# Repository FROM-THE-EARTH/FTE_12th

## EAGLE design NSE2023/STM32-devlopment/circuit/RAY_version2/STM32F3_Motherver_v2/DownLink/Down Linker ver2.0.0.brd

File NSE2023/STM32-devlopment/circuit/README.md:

# circuit

## 開発の流れ
RAY電装の開発は以下のような流れで行いました。
1. ブレッドボード上でのSTM32F303K8の動作試験
2. PCB基板上での書き込み試験(LED点灯プログラム)
3. PCB基板上でのprintfデバッグ
4. PCB基板上でのサーボモーターの動作試験
5. PCB基板上でのI2Cデバイスの動作試験(BNO055,BMP180)
6. PCB基板上でのSDカードの動作試験
7. PCB基板上でのUARTデバイスの動作試験(GPS,RM92A)  

各項目について、詳細な手順を以下に記載します。
### ブレッドボード上でのSTM32F303K8の動作試験
電装製作において最も重要なことは手を動かすことです。未知な要素が多いマイコンを扱う際は、早めに部品を発注して動作試験をしましょう。
筆者はまず[このサイト](https://yoshikiyo.com/2021/01/04/20210104/)を参考にSTM32の動作試験を行いました。実際に使用した部品を以下に記載します。
* [STM32F303K8](https://akizukidenshi.com/catalog/g/gI-10790/)
* [32ピンQFR変換基板](https://akizukidenshi.com/catalog/g/gP-09581/)
* [STLink](https://www.amazon.co.jp/QuiExact-%E3%83%97%E3%83%AD%E3%82%B0%E3%83%A9%E3%83%9F%E3%83%B3%E3%82%B0%E3%82%AD%E3%83%83%E3%83%88-%E3%82%A8%E3%83%9F%E3%83%A5%E3%83%AC%E3%83%BC%E3%82%BF%E3%83%87%E3%83%90%E3%83%83%E3%82%AC-%E3%82%B7%E3%83%9F%E3%83%A5%E3%83%AC%E3%83%BC%E3%82%B7%E3%83%A7%E3%83%B3-%E3%83%87%E3%83%90%E3%83%83%E3%82%AC%E3%82%A8%E3%83%9F%E3%83%A5%E3%83%AC%E3%83%BC%E3%82%BF/dp/B0B5KLKDY2/ref=sr_1_1_sspa?keywords=st-link%2Fv2&qid=1698780781&sr=8-1-spons&sp_csd=d2lkZ2V0TmFtZT1zcF9hdGY&psc=1)

接続するピンさえ間違えなければ、サイトの手順に従うことでLEDの点灯プログラムの動作試験を完了させることができると思います。
マイコンボードと違いUSBインターフェースがないため、書き込みにはSTLinkと呼ばれる専用の書き込み装置を用いる必要があります。中華性の格安STLinkではなく、純正品を使用することをおすすめします。

### PCB基板上での書き込み試験(LED点灯プログラム)
上記のサイトをもとに、以下のような回路を設計しました。

電源系はサイトに準拠し、I2Cデバイス(BNO055, BMP180)及びmicroSDのインターフェースを設けました。この基板を用いてLED点灯プログラム及びprintfデバッグ、I2Cデバイスの動作試験を正常に行うことができました。この基板でのSDカードの書き込みには成功していないため、SDカードの動作試験には別基板を用いる必要があります。(後述)

### PCB基板上でのprintfデバッグ
マイコンからPCへのデータの送信を確立することは組み込み開発における必須事項です。マイコンボードを使用する場合はUSBインターフェースがあるため別途容易する必要はありませんが、マイコン単体から開発する場合は自分で回路上にPC用のインターフェースを用意する必要があります。  

STM32マイコンにはSWOと呼ばれるピンが用意されており、手元にあるSTLinkのSWOピンと接続することで、SWO通信を利用することができます。SWOはUARTのTXピンと同等の役割を果たし、マイコンからPCにprintfを介してデータを送信することができます。  

筆者は[このサイト](https://yukblog.net/stm32cubeide-printf-swo/)をもとにSWOによるprintfの動作試験を行いました。基本的にはサイトに従う形でかまいませんが、1.12以降のCubeIDEを用いる場合は追加で以下の設定が必要です。
project内のiocファイルを開き、System Core > SYSを加え、写真の通りに設定を行ってください。

これにより、printfツールを正常に使用することができるはずです。また、printfツールでfloat型の変数を表示したい場合は[追加設定](https://yukblog.net/stm32cubeide-printf-float/)が必要です。　　

陥りやすいミスと対策法を以下に示します。
* STLinkとの接続ミス(ピンの名前が書いてないため間違えやすい)
* 過剰に高い周波数で動作させている。外部発振器を用いない場合STM32F303K8で利用可能な最大周波数は64MHzですが、32MHz程度で動作させることを推奨します。ロケット電装でそこまで高周波で動作することは求められることはありませんし、高周波になるほどノイズがのりやすくなります。
* プログラムに問題があるか、表示のさせ方に問題があるかを明らかにするために、オシロスコープを用いることを推奨します。オシロスコープのプローブをGNDとSWOピンに接続し、そもそも信号が走っているかを確認しましょう。

### PCB基板上でのサーボモーターの動作試験
サーボモーターの駆動にはPWM信号を出力する必要があり、PWM信号の出力にはタイマーの利用が必須です。  
STM32F303K8ではTIM1,2,3,6,7,15,16,17の合計8つのタイマーを利用することができます。SWOやUARTもタイマーを使用するため、空き状況をみて適切なタイマーを選択してください。筆者はTIM2のchannel1を使用しています。

```cpp
/* USER CODE BEGIN 2 */
	HAL_TIM_PWM_Start(&htim2, TIM_CHANNEL_1); //initialize PWM
/* USER CODE END 2 */
```

サーボモーターの動作試験に関して最も参考になるのは[このサイト](https://qiita.com/usashirou/items/2d0fedf59a3cef083b87)だと思います。  
参考までに筆者の動作試験時の設定を共有します。
* APB1 Timer clocks (MHz) : 44MHz
* Prescaler(PSC - 16 bits value) : 840
* Counter Period : 1048

sg90を使用する場合は以下の関数をそのまま流用することができます。
```cpp
/* USER CODE BEGIN 4 */
void servoWrite(int angle) {
	// Calculate pulse value based on the angle
	int pulseValue = 25 + angle * (120 - 25) / 180;

	// Ensure pulseValue is within valid range
	if (pulseValue > 120) {
		pulseValue = 120;
	}

	// Set the pulse width using TIM2 and specified channel
	__HAL_TIM_SET_COMPARE(&htim2, TIM_CHANNEL_1, pulseValue);
}
/* USER CODE END 4 */
```

### PCB基板上でのI2Cデバイスの動作試験
特別な設定はいりません。詳細は /software に記載します。

### PCB基板上でのSDカードの動作試験
おそらく最も苦戦するのがSDカードの書き込みです。ここでは回路上の注意事項を述べたいと思います。

SDカードの書き込みにはSPI通信を用いています。SPI通信は大容量のデータ転送を可能にする高速な通信ですが、高周波であるためにノイズに弱いという特性を持っています。配線時にノイズを軽減する配慮をしなければ、書き込みに失敗してしまうでしょう。以下にノイズを軽減する有効な手段を示します。
* MISO, MOSI, CLKラインのプルアップ。1k~10kの抵抗でプルアップしてください。筆者は1kΩの抵抗を使用していました。
* ダンピング抵抗の設置。CLK出力ピンの直後に100Ω程度の抵抗を配置することで、ノイズを減衰させることができます。[(参考サイト)](https://ally-japan.jimdo.com/2015/11/23/%E3%82%AF%E3%83%AD%E3%83%83%E3%82%AF%E3%81%AB%E3%81%A4%E3%81%84%E3%81%A6-part2/)
* 配線の最短化。基本的に、配線は長いほど、細いほどノイズがのりやすくなります。SDカードへの配線は可能な限り短く、太くすべきです。

完全ではありませんが、上記の3点に留意した以下の基板では、SDカードの書き込みに成功しています。  

### PCB基板上でのUARTデバイスの動作試験
GPS、RM92Aともに特別な設定はいりませんが、RM92Aは13期代にとって初めて使用する無線モジュールになるので、簡単な使用法をここで紹介します。  
回路の情報は[データシート](http://www.cec-chiyoda.co.jp/document/rflink_RM-92A_RM-92C.pdf)を参考にしてください。一般的な無線モジュールと同様にRX,TXのピンをマイコンに接続すれば問題なく使用することができます。  
データシートに従えば回路構成は以下のようになります。 
  
PIN13は無線のパラメータ設定時にHIGHとLOWを切り替える必要があるため、図のようにスライドスイッチを介してGNDに接続しています。  
RM92Aを導入した背景は、IM920では海打ち機体において十分な通信距離を確保できないため、より長い距離通信できる無線モジュールが必要だったからです。RM92Aは見通し最大100kmの通信が可能であり、一般的な条件下でも10km以上の通信が可能であると言われています。特別な理由がなければ海打ち機体にはIM920ではなくRM92Aを搭載することを推奨します。

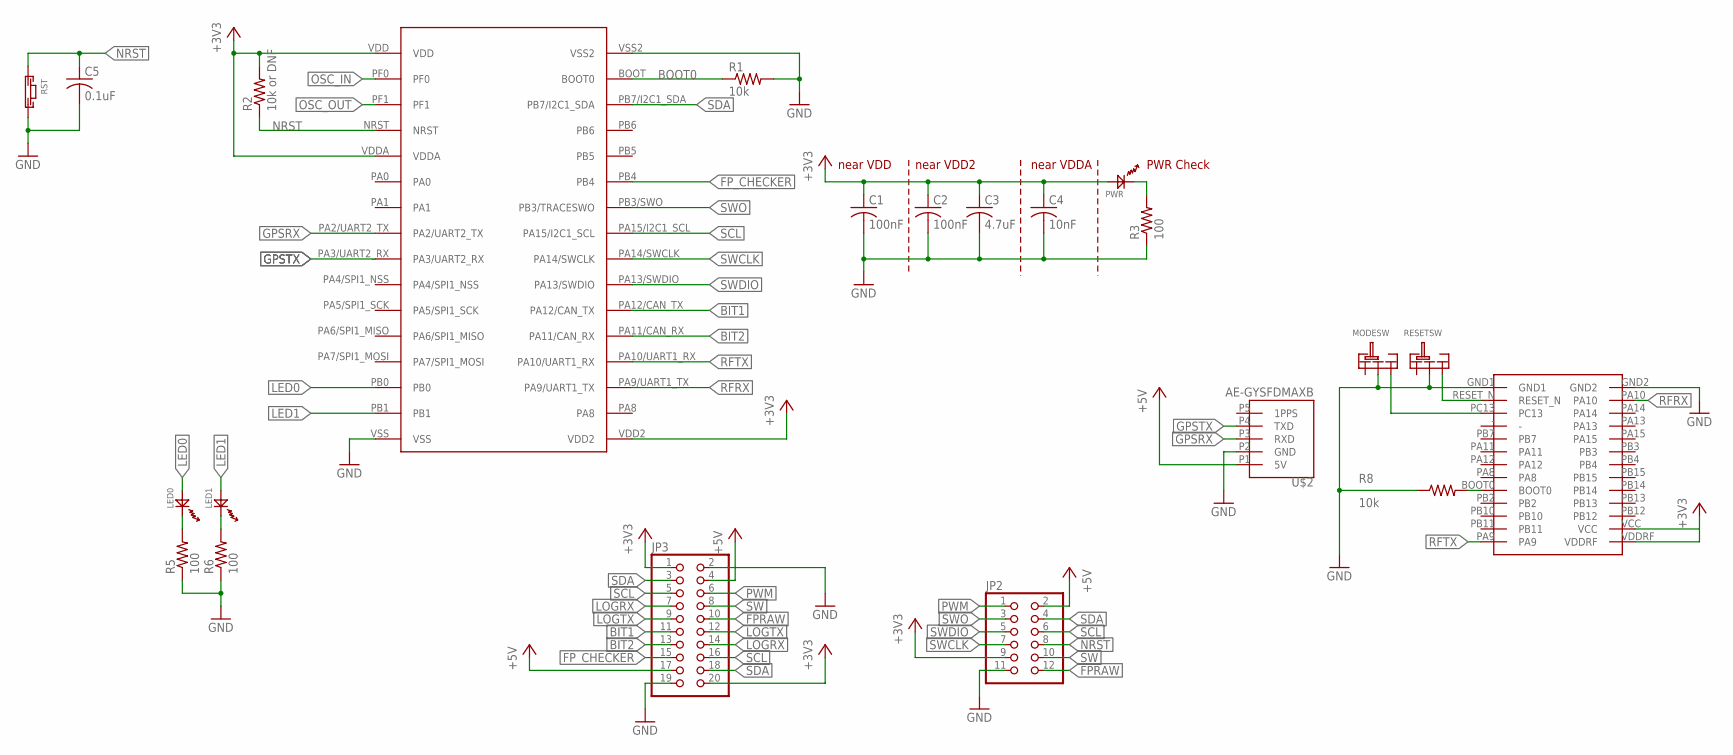
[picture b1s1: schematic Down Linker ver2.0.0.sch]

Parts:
C1, C2: 100nF; C1608
C3: 4.7uF; C1608
C4: 10nF; C1608
C5: 0.1uF; C1608
JP2: PINHD-2X6/90; 2X06/90
JP3: PINHD-2X10/90; 2X10/90
LED0, LED1: OSXX1608C1A
MODESW: SRIDE_SWITCH
PWR: OSXX1608C1A
R1, R8: 10k; R0603
R2: 10k or DNF; R0603
R3, R5, R6: 100; R0603
RESETSW: SRIDE_SWITCH
RST: TVAF06-A020B-R
U$1: STM32F303K8
U$2: AE-GYSFDMAXB
U$3: RM-92A

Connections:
+3V3: C1.1, C2.1, C3.1, C4.1, JP2.9, JP3.1, JP3.20, PWR.AN, R2.2, U$1.VDD, U$1.VDD2, U$1.VDDA, U$3.VCC, U$3.VDDRF
+5V: JP2.2, JP3.4, JP3.17, U$2.P1 (5V)
BIT1: JP3.11, U$1.PA12/CAN_TX
BIT2: JP3.13, U$1.PA11/CAN_RX
BOOT0: R1.1, U$1.BOOT (BOOT0)
FPRAW: JP2.12, JP3.10
FP_CHECKER: JP3.15, U$1.PB4
GND: C1.2, C2.2, C3.2, C4.2, C5.2, JP2.11, JP3.2, JP3.19, MODESW.LR, R1.2, R3.1, R5.1, R6.1, R8.1, RESETSW.LR, RST.P$2, U$1.VSS, U$1.VSS2, U$2.P2 (GND), U$3.GND1, U$3.GND2
GPSRX: U$1.PA2/UART2_TX, U$2.P3 (RXD)
GPSTX: U$1.PA3/UART2_RX, U$2.P4 (TXD)
LED0: LED0.AN, U$1.PB0
LED1: LED1.AN, U$1.PB1
LOGRX: JP3.7, JP3.14
LOGTX: JP3.9, JP3.12
unnamed: PWR.CT, R3.2
unnamed: LED0.CT, R5.2
unnamed: LED1.CT, R6.2
unnamed: MODESW.R, U$3.PC13
unnamed: RESETSW.R, U$3.RESET_N
unnamed: R8.2, U$3.BOOT0
NRST: C5.1, JP2.8, R2.1, RST.P$1, U$1.NRST
OSC_IN: U$1.PF0
OSC_OUT: U$1.PF1
PWM: JP2.1, JP3.6
RFRX: U$1.PA9/UART1_TX, U$3.PA10
RFTX: U$1.PA10/UART1_RX, U$3.PA9
SCL: JP2.6, JP3.5, JP3.16, U$1.PA15/I2C1_SCL
SDA: JP2.4, JP3.3, JP3.18, U$1.PB7/I2C1_SDA
SW: JP2.10, JP3.8
SWCLK: JP2.7, U$1.PA14/SWCLK
SWDIO: JP2.5, U$1.PA13/SWDIO
SWO: JP2.3, U$1.PB3/SWO (PB3/TRACESWO)

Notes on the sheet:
near VDD
near VDD2
near VDDA
PWR Check

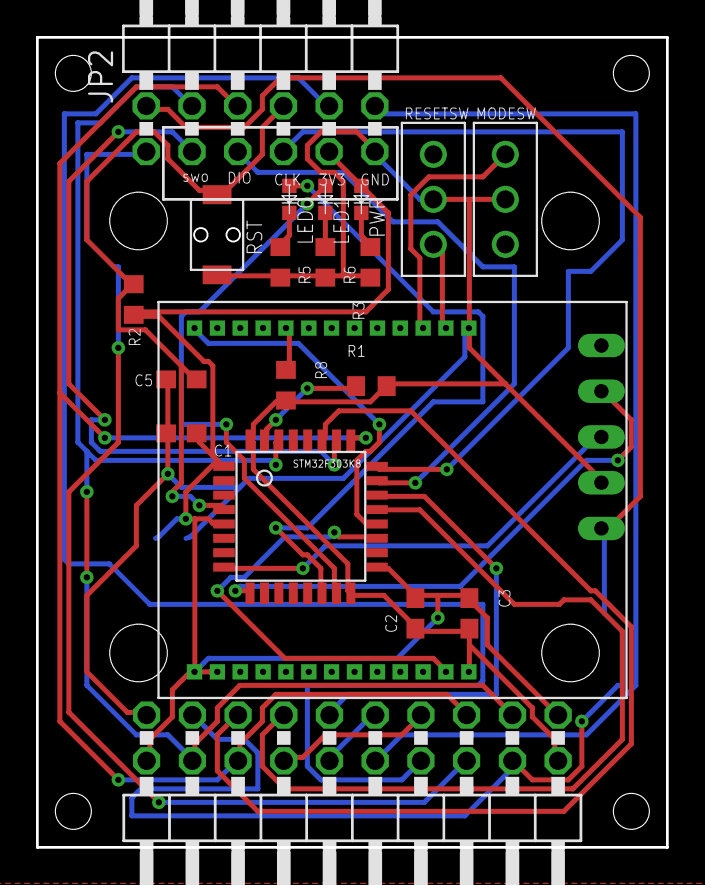
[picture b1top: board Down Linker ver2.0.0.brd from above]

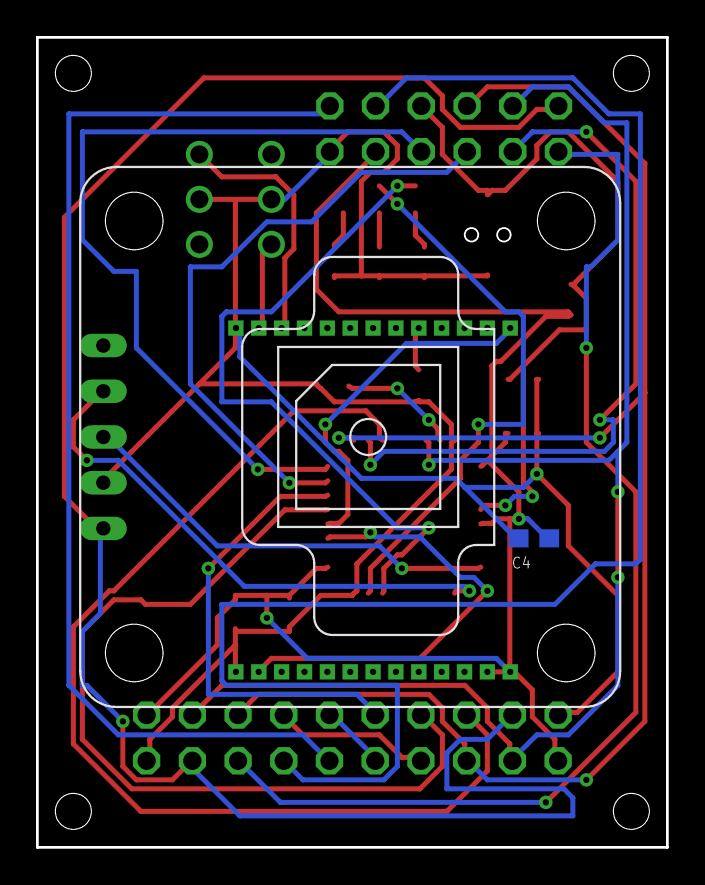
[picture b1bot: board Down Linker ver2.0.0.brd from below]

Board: 2 copper layers, 35.0 x 45.0 mm, 22 parts (2 on the bottom side), 30 nets.

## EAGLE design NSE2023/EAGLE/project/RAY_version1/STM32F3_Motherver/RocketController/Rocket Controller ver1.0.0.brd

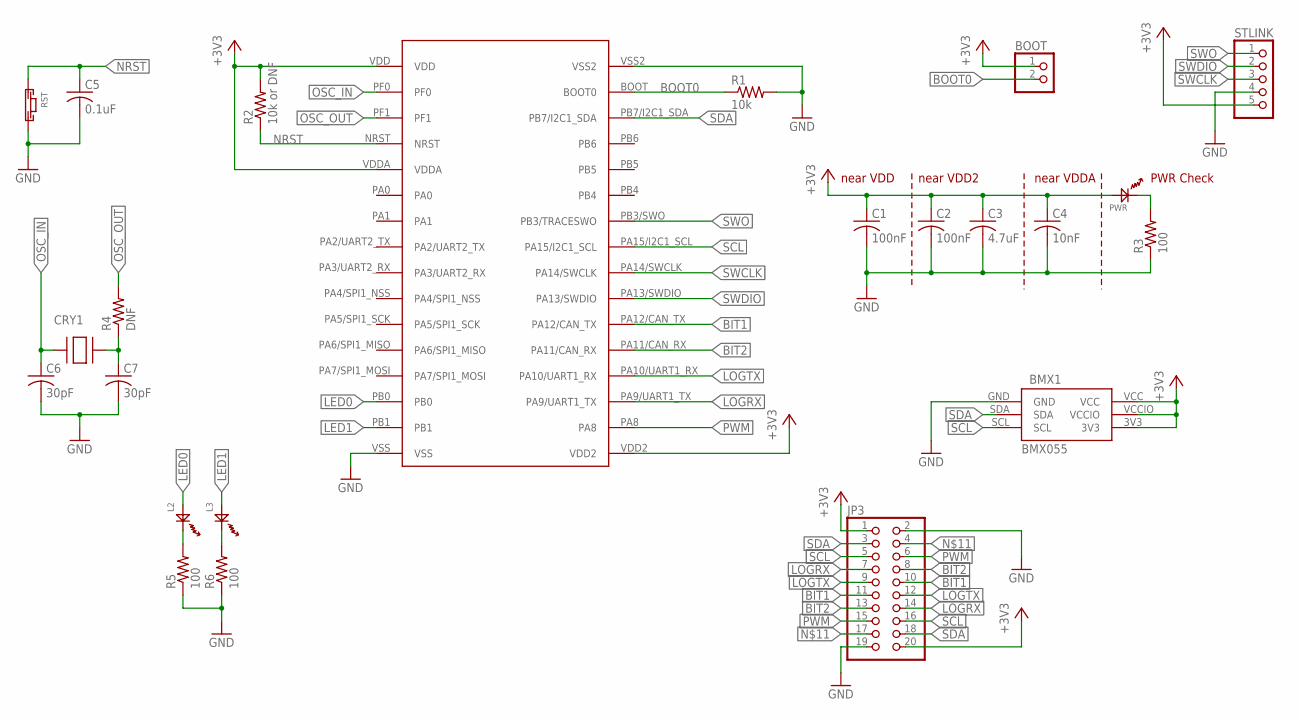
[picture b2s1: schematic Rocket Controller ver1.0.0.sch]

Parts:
BMX1: BMX055
BOOT: PINHD-1X2; 1X02
C1, C2: 100nF; C1608
C3: 4.7uF; C1608
C4: 10nF; C1608
C5: 0.1uF; C1608
C6, C7: 30pF; C1608
CRY1: 8MHZ; CRYSTAL
JP3: PINHD-2X10/90; 2X10/90
L2, L3: OSXX1608C1A
PWR: OSXX1608C1A
R1: 10k; R0603
R2: 10k or DNF; R0603
R3, R5, R6: 100; R0603
R4: DNF; R0603
RST: TVAF06-A020B-R
STLINK: PINHD-1X5; 1X05
U$1: STM32F303K8

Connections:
+3V3: BMX1.3V3, BMX1.VCC, BMX1.VCCIO, BOOT.1, C1.1, C2.1, C3.1, C4.1, JP3.1, JP3.20, PWR.AN, R2.2, STLINK.5, U$1.VDD, U$1.VDD2, U$1.VDDA
BIT1: JP3.10, JP3.11, U$1.PA12/CAN_TX
BIT2: JP3.8, JP3.13, U$1.PA11/CAN_RX
BOOT0: BOOT.2, R1.1, U$1.BOOT (BOOT0)
GND: BMX1.GND, C1.2, C2.2, C3.2, C4.2, C5.2, C6.2, C7.2, JP3.2, JP3.19, R1.2, R3.1, R5.1, R6.1, RST.P$2, STLINK.4, U$1.VSS, U$1.VSS2
LED0: L2.AN, U$1.PB0
LED1: L3.AN, U$1.PB1
LOGRX: JP3.7, JP3.14, U$1.PA9/UART1_TX
LOGTX: JP3.9, JP3.12, U$1.PA10/UART1_RX
unnamed: PWR.CT, R3.2
unnamed: L2.CT, R5.2
unnamed: C7.1, CRY1.P$2, R4.1
unnamed: L3.CT, R6.2
unnamed: JP3.4, JP3.17
NRST: C5.1, R2.1, RST.P$1, U$1.NRST
OSC_IN: C6.1, CRY1.P$1, U$1.PF0
OSC_OUT: R4.2, U$1.PF1
PWM: JP3.6, JP3.15, U$1.PA8
SCL: BMX1.SCL, JP3.5, JP3.16, U$1.PA15/I2C1_SCL
SDA: BMX1.SDA, JP3.3, JP3.18, U$1.PB7/I2C1_SDA
SWCLK: STLINK.3, U$1.PA14/SWCLK
SWDIO: STLINK.2, U$1.PA13/SWDIO
SWO: STLINK.1, U$1.PB3/SWO (PB3/TRACESWO)

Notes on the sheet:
near VDD
near VDD2
near VDDA
PWR Check

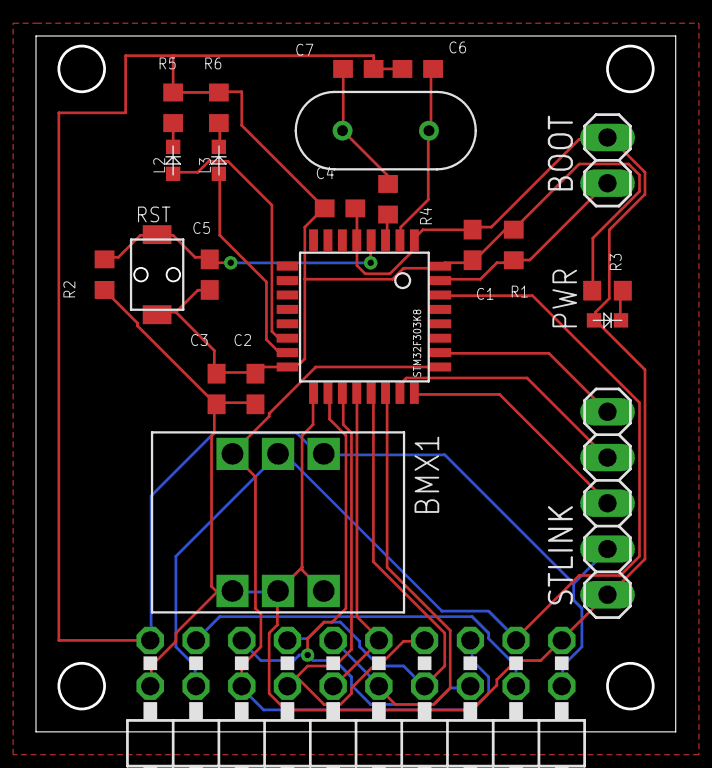
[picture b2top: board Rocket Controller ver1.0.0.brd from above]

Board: 2 copper layers, 35.4 x 38.5 mm, 23 parts (0 on the bottom side), 23 nets.

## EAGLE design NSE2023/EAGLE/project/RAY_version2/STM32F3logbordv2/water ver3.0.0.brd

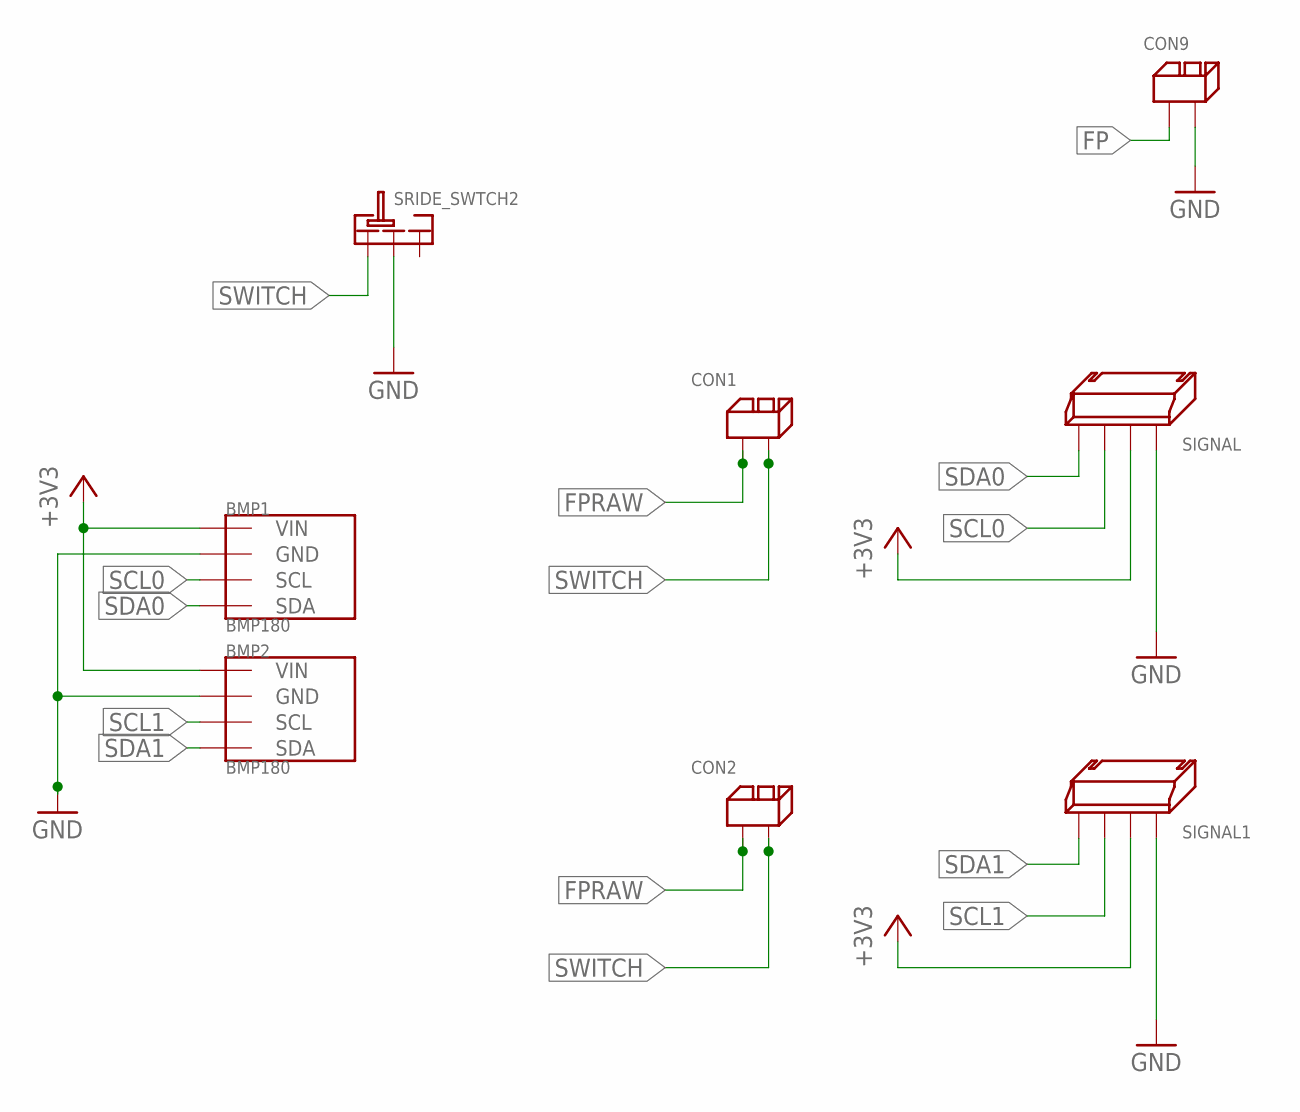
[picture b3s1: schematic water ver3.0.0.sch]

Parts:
BMP1, BMP2: BMP180; GY-68
CON1, CON2, CON9: 2PIN
SIGNAL, SIGNAL1: 4PIN_SIDE
SRIDE_SWTCH2: SRIDE_SWITCH

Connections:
+3V3: BMP1.P1 (VIN), BMP2.P1 (VIN), SIGNAL.P$3, SIGNAL1.P$3
FP: CON9.P$1
FPRAW: CON1.P$1, CON2.P$1
GND: BMP1.P2 (GND), BMP2.P2 (GND), CON9.P$2, SIGNAL.P$4, SIGNAL1.P$4, SRIDE_SWTCH2.LR
SCL0: BMP1.P3 (SCL), SIGNAL.P$1
SCL1: BMP2.P3 (SCL), SIGNAL1.P$1
SDA0: BMP1.P4 (SDA), SIGNAL.P$2
SDA1: BMP2.P4 (SDA), SIGNAL1.P$2
SWITCH: CON1.P$2, CON2.P$2, SRIDE_SWTCH2.L

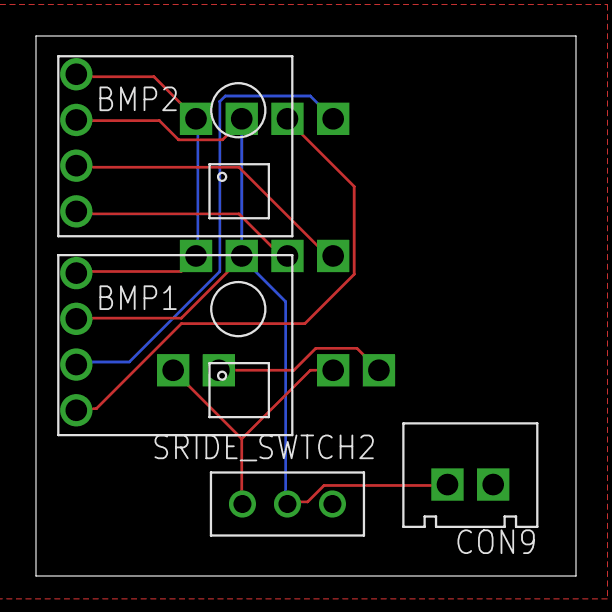
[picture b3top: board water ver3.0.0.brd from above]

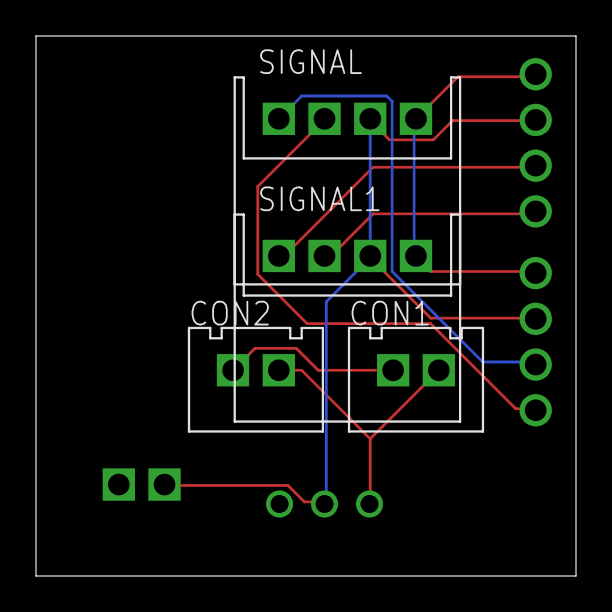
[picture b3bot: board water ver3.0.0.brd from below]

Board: 2 copper layers, 30.0 x 30.0 mm, 8 parts (4 on the bottom side), 8 nets.

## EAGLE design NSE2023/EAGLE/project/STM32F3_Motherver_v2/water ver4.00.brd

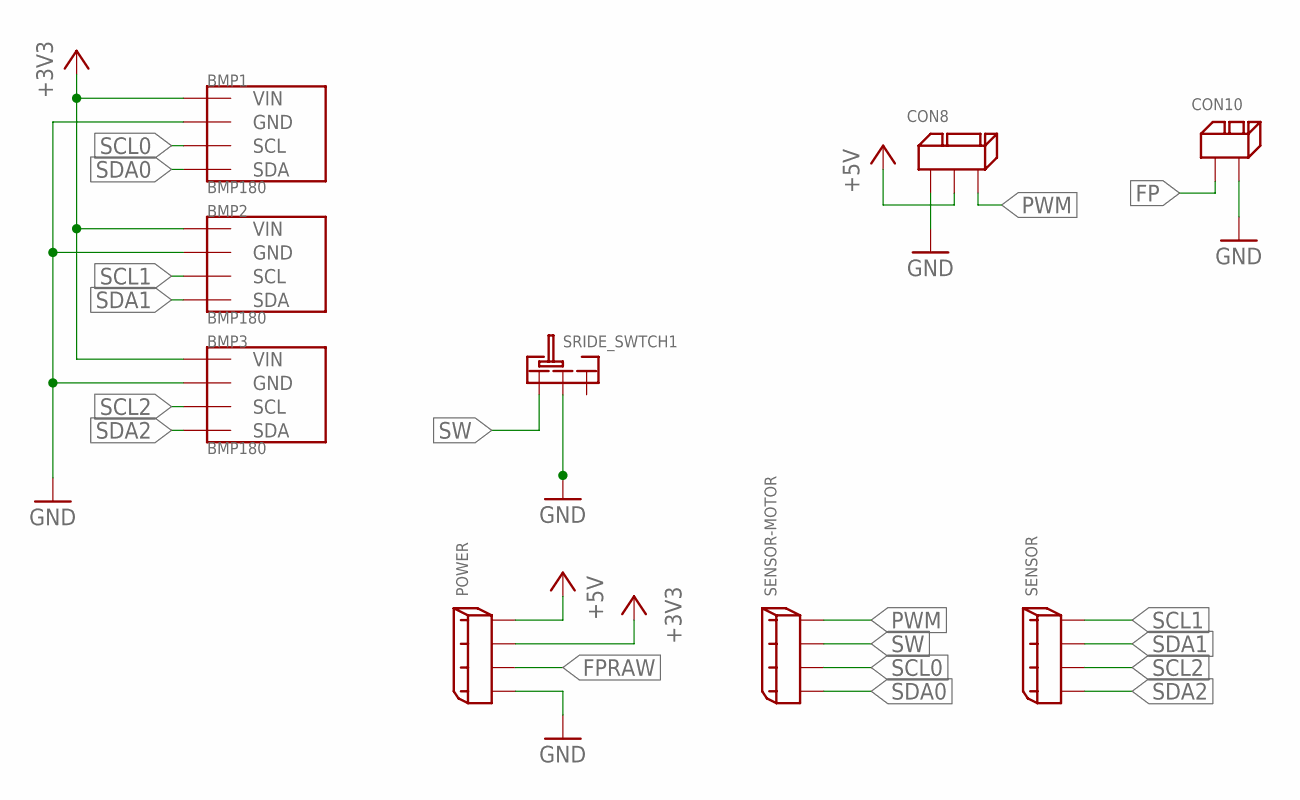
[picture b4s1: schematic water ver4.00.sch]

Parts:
BMP1, BMP2, BMP3: BMP180; GY-68
CON8: 3PIN
CON10: 2PIN
POWER: 2.5_MINI-SPOX_4PIN
SENSOR: 2.5_MINI-SPOX_4PIN
SENSOR-MOTOR: 2.5_MINI-SPOX_4PIN
SRIDE_SWTCH1: SRIDE_SWITCH

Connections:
+3V3: BMP1.P1 (VIN), BMP2.P1 (VIN), BMP3.P1 (VIN), POWER.P$3 (3)
+5V: CON8.P$2, POWER.P$4 (4)
FP: CON10.P$1
FPRAW: POWER.P$2 (2)
GND: BMP1.P2 (GND), BMP2.P2 (GND), BMP3.P2 (GND), CON8.P$1, CON10.P$2, POWER.P$1 (1), SRIDE_SWTCH1.LR
PWM: CON8.P$3, SENSOR-MOTOR.P$4 (4)
SCL0: BMP1.P3 (SCL), SENSOR-MOTOR.P$2 (2)
SCL1: BMP2.P3 (SCL), SENSOR.P$4 (4)
SCL2: BMP3.P3 (SCL), SENSOR.P$2 (2)
SDA0: BMP1.P4 (SDA), SENSOR-MOTOR.P$1 (1)
SDA1: BMP2.P4 (SDA), SENSOR.P$3 (3)
SDA2: BMP3.P4 (SDA), SENSOR.P$1 (1)
SW: SENSOR-MOTOR.P$3 (3), SRIDE_SWTCH1.L

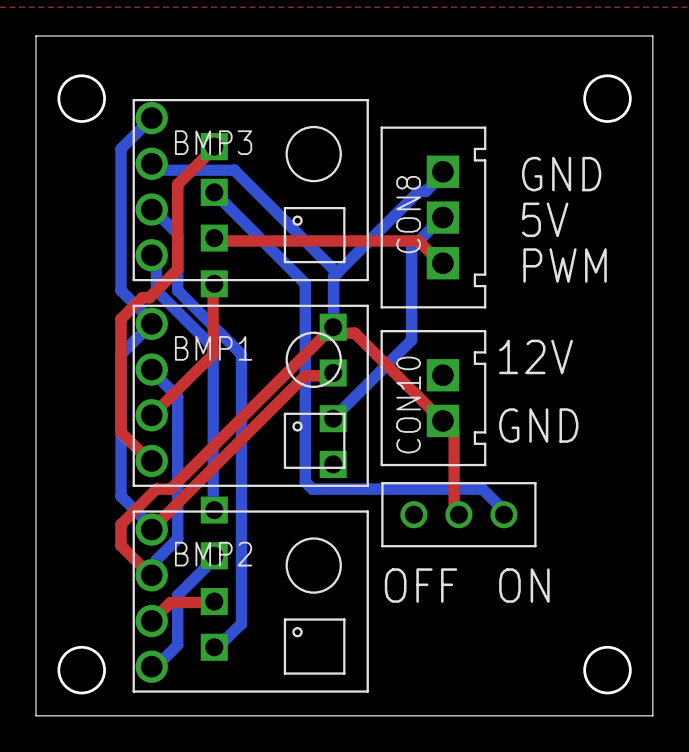
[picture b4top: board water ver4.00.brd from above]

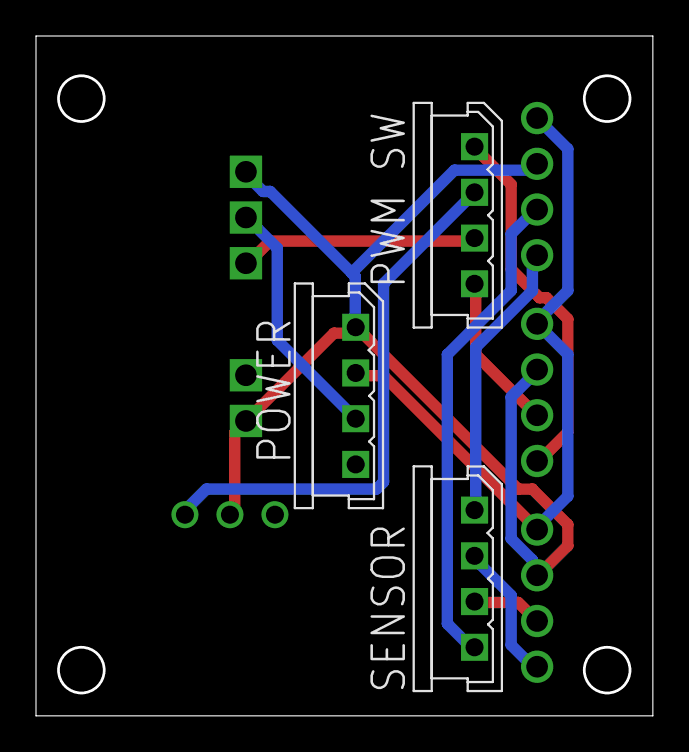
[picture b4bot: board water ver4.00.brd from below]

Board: 2 copper layers, 34.1 x 37.6 mm, 9 parts (3 on the bottom side), 11 nets.

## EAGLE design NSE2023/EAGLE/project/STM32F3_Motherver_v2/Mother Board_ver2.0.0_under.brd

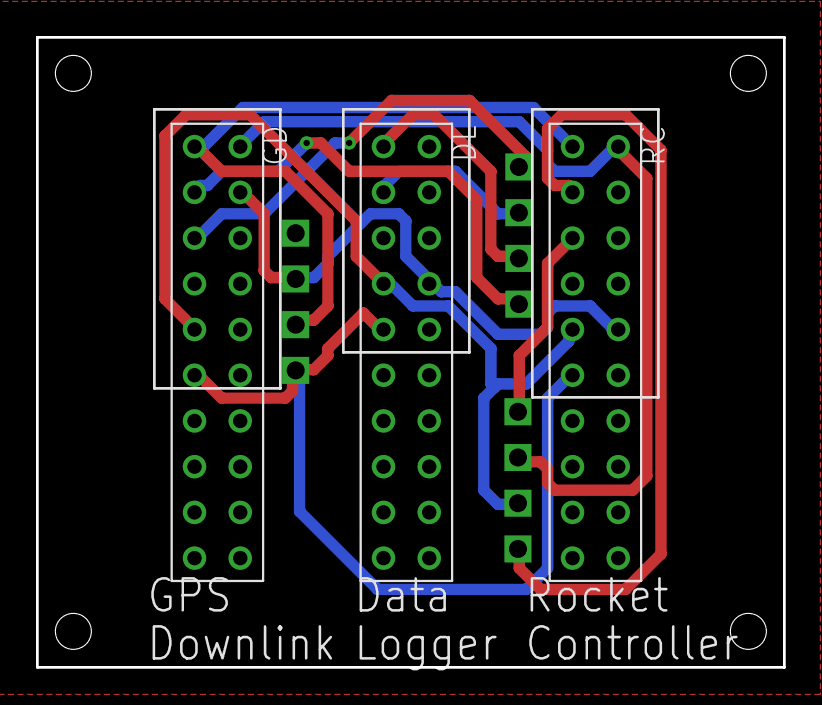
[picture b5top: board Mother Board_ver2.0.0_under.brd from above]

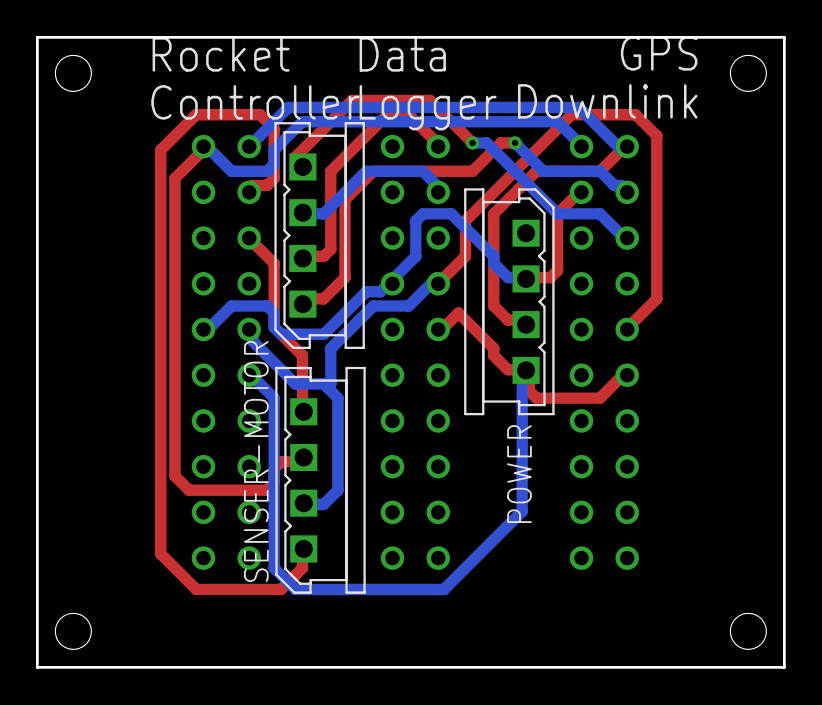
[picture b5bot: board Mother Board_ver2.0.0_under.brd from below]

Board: 2 copper layers, 41.5 x 35.0 mm, 6 parts (3 on the bottom side), 12 nets.

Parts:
CON7: 2.5_MINI-SPOX_4PIN
DL: 2X10
GD: 2X10
POWER: 2.5_MINI-SPOX_4PIN
RC: 2X10
SENSER-MOTOR: 2.5_MINI-SPOX_4PIN

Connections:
+3V3: DL.P$13, GD.P$17, POWER.P$3, RC.P$11
+5V: GD.P$20, POWER.P$4, RC.P$20
FPRAW: DL.P$12, GD.P$10, POWER.P$2, RC.P$10
GND: DL.P$11, GD.P$9, POWER.P$1, RC.P$9
PWM: GD.P$19, RC.P$19, SENSER-MOTOR.P$4
SCL0: RC.P$16, SENSER-MOTOR.P$2
SCL1: CON7.P$4, DL.P$18
SCL2: CON7.P$2, GD.P$16
SDA0: RC.P$18, SENSER-MOTOR.P$1
SDA1: CON7.P$3, DL.P$20
SDA2: CON7.P$1, GD.P$18
SW: DL.P$14, GD.P$12, RC.P$12, SENSER-MOTOR.P$3

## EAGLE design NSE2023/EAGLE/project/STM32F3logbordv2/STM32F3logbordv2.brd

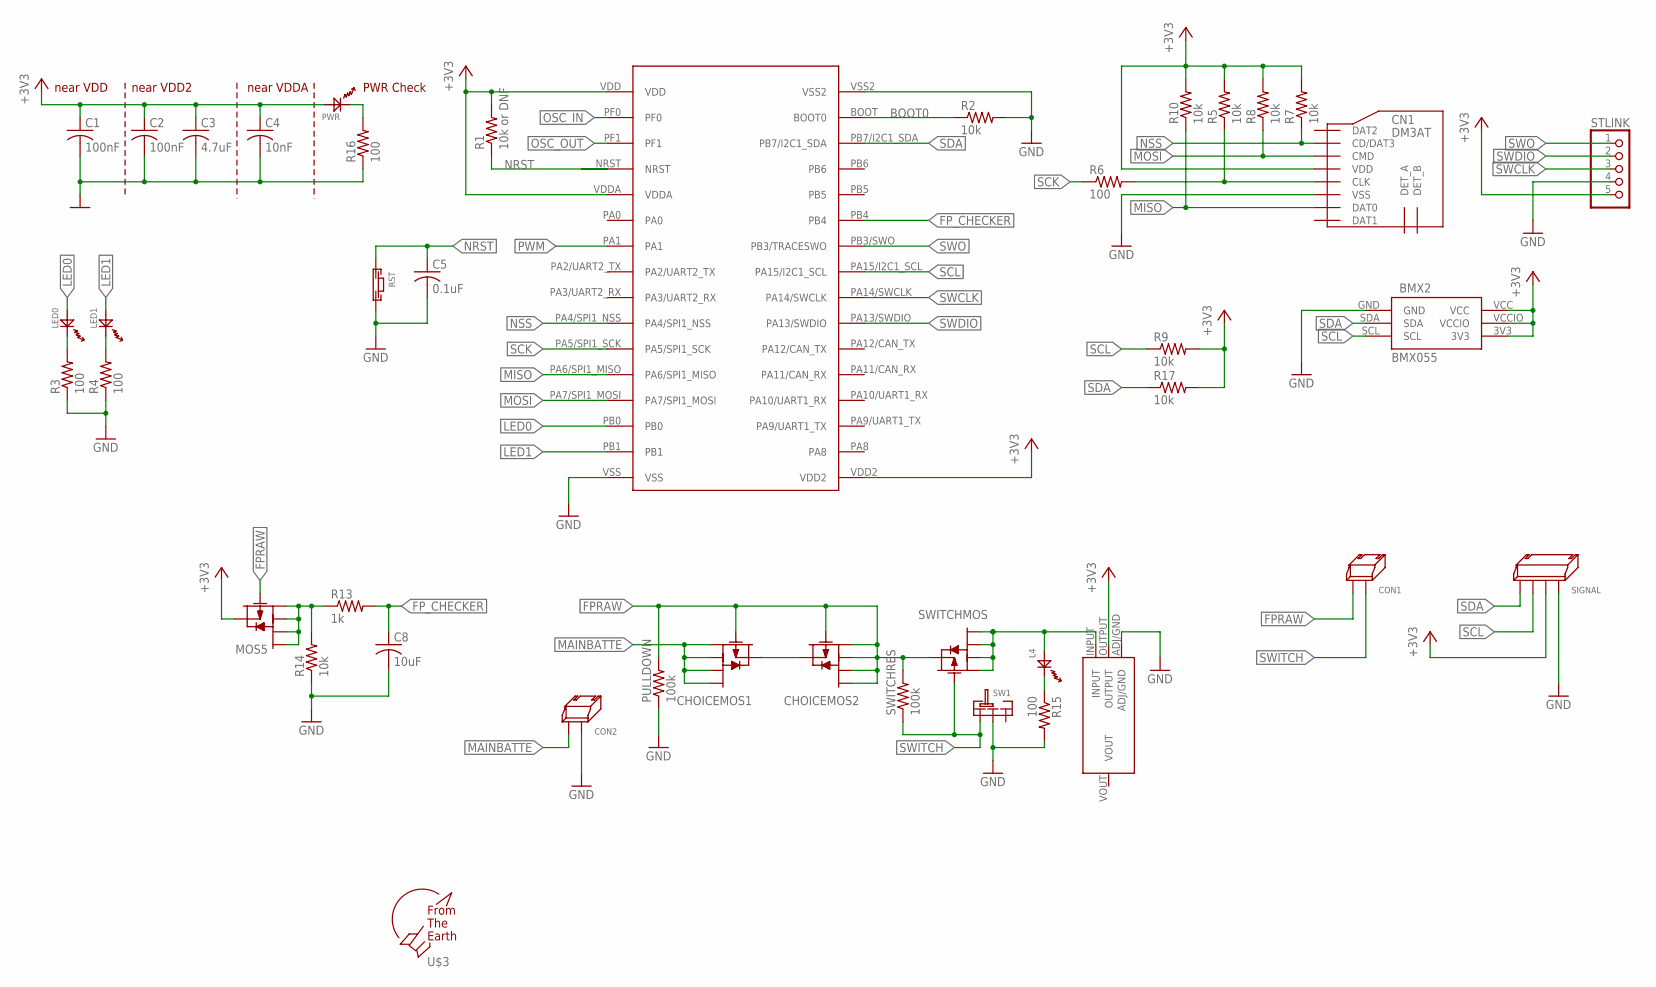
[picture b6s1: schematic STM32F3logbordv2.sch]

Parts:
BMX2: BMX055
C1, C2: 100nF; C1608
C3: 4.7uF; C1608
C4: 10nF; C1608
C5: 0.1uF; C1608
C8: 10uF; C0603
CHOICEMOS1, CHOICEMOS2: PCH_SSM6J808R; SSM6J808R
CN1: DM3AT
CON1, CON2: 2PIN_SIDE
L4: OSXX1608C1A
LED0, LED1: OSXX1608C1A
MOS5: PCH_SSM6J808R; SSM6J808R
PULLDOWN: 100k; R0603
PWR: OSXX1608C1A
R1: 10k or DNF; R0603
R2, R5, R7, R8, R9, R10, R14, R17: 10k; R0603
R3, R4, R6, R15, R16: 100; R0603
R13: 1k; R0603
RST: TVAF06-A020B-R
SIGNAL: 4PIN_SIDE
STLINK: PINHD-1X5/90; 1X05/90
SW1: SRIDE_SWITCH
SWITCHMOS: PCH_SSM6J808R; SSM6J808R
SWITCHRES: 100k; R0603
U$1: STM32F303K8
U$3: F.T.E.LOGO; LOGO
U$4: AZ1117C

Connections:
+3V3: BMX2.3V3, BMX2.VCC, BMX2.VCCIO, C1.1, C2.1, C3.1, C4.1, CN1.VDD, MOS5.4, PWR.AN, R1.2, R5.2, R7.2, R8.2, R9.2, R10.2, R17.2, SIGNAL.P$3, STLINK.5, U$1.VDD, U$1.VDD2, U$1.VDDA, U$4.OUTPUT
BOOT0: R2.1, U$1.BOOT (BOOT0)
FPRAW: CHOICEMOS1.3, CHOICEMOS2.1, CHOICEMOS2.2, CHOICEMOS2.3, CHOICEMOS2.5, CHOICEMOS2.6, CON1.P$2, MOS5.3, PULLDOWN.2, SWITCHMOS.4, SWITCHRES.2
FP_CHECKER: C8.1, R13.2, U$1.PB4
GND: BMX2.GND, C1.2, C2.2, C3.2, C4.2, C5.2, C8.2, CN1.VSS, CON2.P$1, PULLDOWN.1, R2.2, R3.1, R4.1, R14.1, R15.2, R16.1, RST.P$2, SIGNAL.P$4, STLINK.4, SW1.LR, U$1.VSS, U$1.VSS2, U$4.ADJ/GND
LED0: LED0.AN, U$1.PB0
LED1: LED1.AN, U$1.PB1
MAINBATTE: CHOICEMOS1.1, CHOICEMOS1.2, CHOICEMOS1.5, CHOICEMOS1.6, CON2.P$2
MISO: CN1.DAT0, R10.1, U$1.PA6/SPI1_MISO
MOSI: CN1.CMD, R8.1, U$1.PA7/SPI1_MOSI
unnamed: PWR.CT, R16.2
unnamed: LED0.CT, R3.2
unnamed: LED1.CT, R4.2
unnamed: CN1.CLK, R5.1, R6.2
unnamed: CHOICEMOS1.4, CHOICEMOS2.4
unnamed: L4.AN, SWITCHMOS.1, SWITCHMOS.2, SWITCHMOS.5, SWITCHMOS.6, U$4.INPUT
unnamed: MOS5.1, MOS5.2, MOS5.5, MOS5.6, R13.1, R14.2
unnamed: L4.CT, R15.1
NRST: C5.1, R1.1, RST.P$1
NSS: CN1.CD/DAT3, R7.1, U$1.PA4/SPI1_NSS
OSC_IN: U$1.PF0
OSC_OUT: U$1.PF1
PWM: U$1.PA1
SCK: R6.1, U$1.PA5/SPI1_SCK
SCL: BMX2.SCL, R9.1, SIGNAL.P$1, U$1.PA15/I2C1_SCL
SDA: BMX2.SDA, R17.1, SIGNAL.P$2, U$1.PB7/I2C1_SDA
SWCLK: STLINK.3, U$1.PA14/SWCLK
SWDIO: STLINK.2, U$1.PA13/SWDIO
SWITCH: CON1.P$1, SW1.L, SWITCHMOS.3, SWITCHRES.1
SWO: STLINK.1, U$1.PB3/SWO (PB3/TRACESWO)

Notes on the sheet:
near VDD
near VDD2
near VDDA
PWR Check

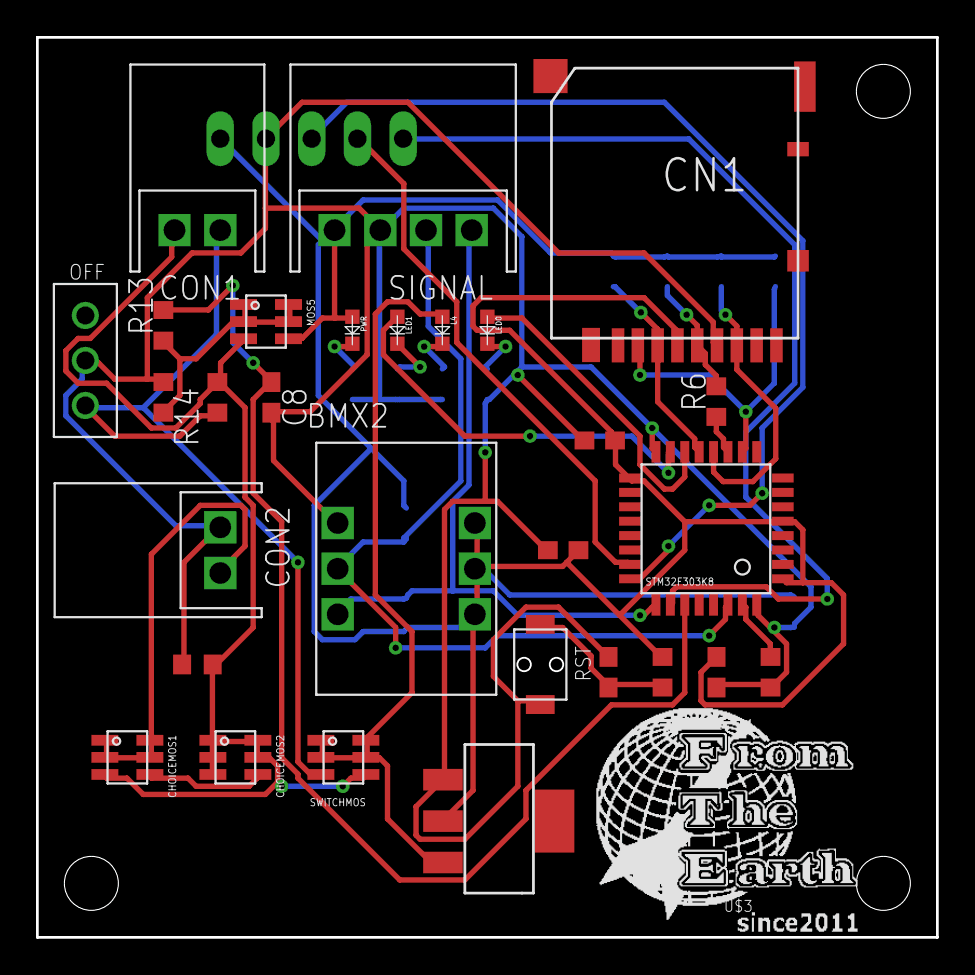
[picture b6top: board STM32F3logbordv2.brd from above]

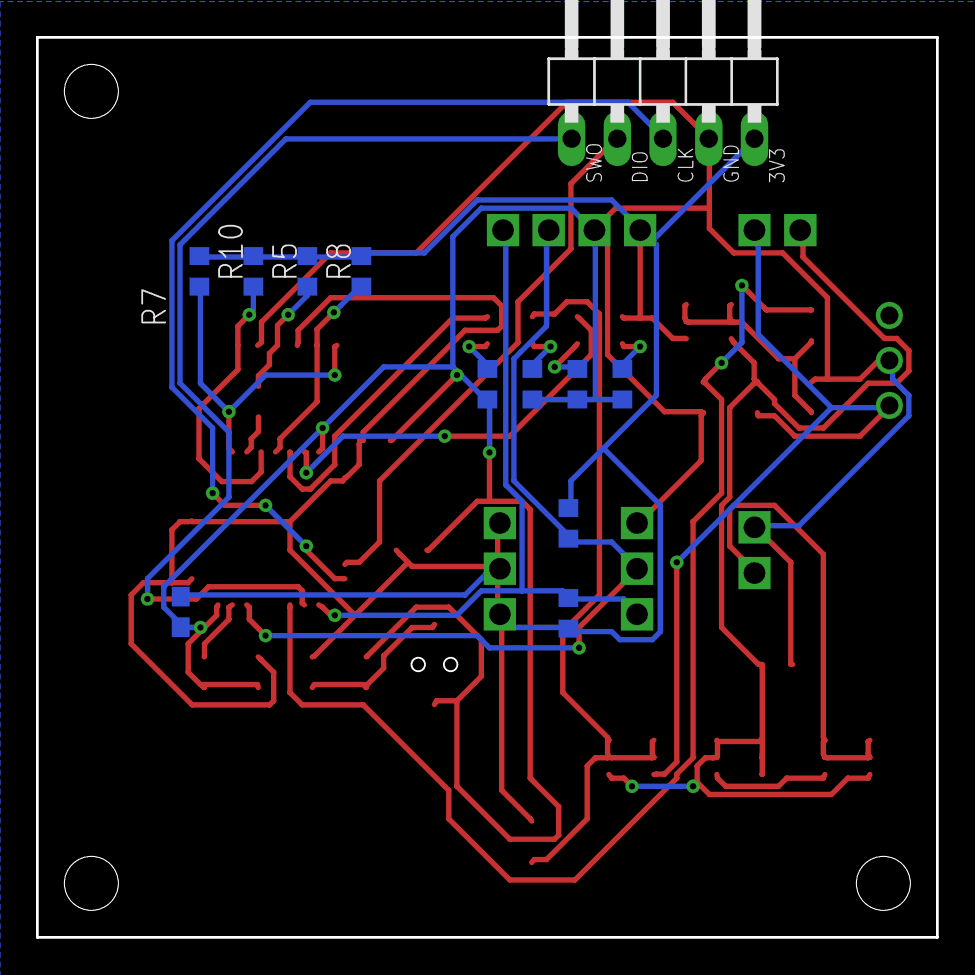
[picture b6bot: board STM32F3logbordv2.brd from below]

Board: 2 copper layers, 50.0 x 50.0 mm, 42 parts (12 on the bottom side), 27 nets.

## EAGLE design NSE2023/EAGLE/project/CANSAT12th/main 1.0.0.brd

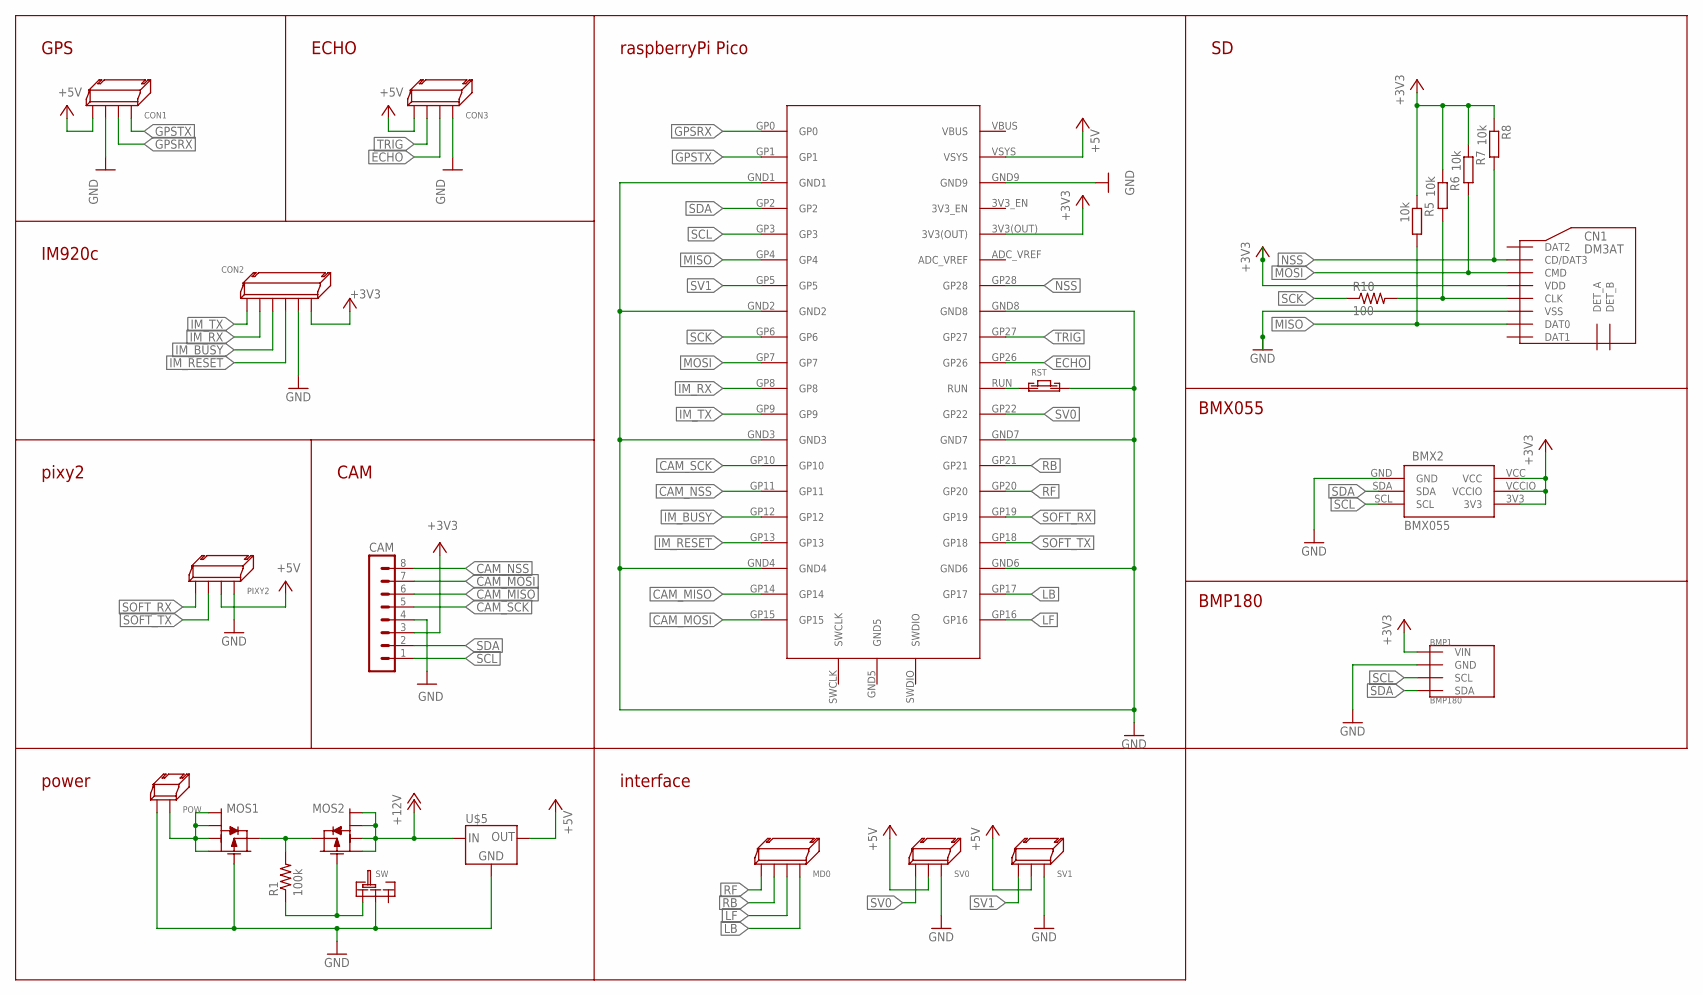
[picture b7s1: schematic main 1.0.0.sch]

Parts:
BMP1: BMP180; GY-68
BMX2: BMX055
CAM: MA08-1
CN1: DM3AT
CON1, CON3: 4PIN_SIDE
CON2: 6PIN_SIDE
MD0: 4PIN_SIDE
MOS1, MOS2: PCH_SSM6J808R; SSM6J808R
PIXY2: 4PIN_SIDE
POW: 2PIN_SIDE
R1: 100k; R0603
R5, R6, R7, R8: 10k; R0603
R10: 100; R0603
RST: TVAF06-A020B-R
SV0, SV1: 3PIN_SIDE
SW: SRIDE_SWITCH
U$1: RASPBERRYPIPICO
U$5: LT1117-5; SOT-223

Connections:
1: CN1.CLK, R6.2, R10.2
+3V3: BMP1.P1 (VIN), BMX2.3V3, BMX2.VCC, BMX2.VCCIO, CAM.3, CN1.VDD, CON2.P$6, R5.1, R6.1, R7.1, R8.1, U$1.3V3(OUT)
+5V: CON1.P$2, CON3.P$2, PIXY2.P$3, SV0.P$1, SV1.P$1, U$1.VSYS, U$5.2 (OUT)
+12V: MOS2.1, MOS2.2, MOS2.5, MOS2.6, U$5.3 (IN)
CAM_MISO: CAM.6, U$1.GP14
CAM_MOSI: CAM.7, U$1.GP15
CAM_NSS: CAM.8, U$1.GP11
CAM_SCK: CAM.5, U$1.GP10
ECHO: CON3.P$3, U$1.GP26
GND: BMP1.P2 (GND), BMX2.GND, CAM.4, CN1.VSS, CON1.P$1, CON2.P$5, CON3.P$4, MOS1.3, PIXY2.P$4, POW.P$2, RST.P$2, SV0.P$3, SV1.P$3, SW.LR, U$1.GND1, U$1.GND2, U$1.GND3, U$1.GND4, U$1.GND6, U$1.GND7, U$1.GND8, U$5.4 (GND)
GPSRX: CON1.P$3, U$1.GP0
GPSTX: CON1.P$4, U$1.GP1
IM_BUSY: CON2.P$3, U$1.GP12
IM_RESET: CON2.P$4, U$1.GP13
IM_RX: CON2.P$2, U$1.GP8
IM_TX: CON2.P$1, U$1.GP9
LB: MD0.P$4, U$1.GP17
LF: MD0.P$3, U$1.GP16
MISO: CN1.DAT0, R5.2, U$1.GP4
MOSI: CN1.CMD, R7.2, U$1.GP7
unnamed: RST.P$1, U$1.RUN
unnamed: MOS1.4, MOS2.4, R1.2
unnamed: MOS2.3, R1.1, SW.L
unnamed: MOS1.1, MOS1.2, MOS1.5, MOS1.6, POW.P$1
NSS: CN1.CD/DAT3, R8.2, U$1.GP28
RB: MD0.P$1, U$1.GP21
RF: MD0.P$2, U$1.GP20
SCK: R10.1, U$1.GP6
SCL: BMP1.P3 (SCL), BMX2.SCL, CAM.1, U$1.GP3
SDA: BMP1.P4 (SDA), BMX2.SDA, CAM.2, U$1.GP2
SOFT_RX: PIXY2.P$2, U$1.GP19
SOFT_TX: PIXY2.P$1, U$1.GP18
SV0: SV0.P$2, U$1.GP22
SV1: SV1.P$2, U$1.GP5
TRIG: CON3.P$1, U$1.GP27

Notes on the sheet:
BMP180
BMX055
raspberryPi Pico
GPS
IM920c
pixy2
CAM
power
interface
ECHO
